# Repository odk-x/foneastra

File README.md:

# foneastra

This project is __*actively maintained*__

It defines the Foneastra controller board and software for communicating with it.

The developer [wiki](https://github.com/odk-x/tool-suite-X/wiki) (including release notes) and [issues tracker](https://github.com/odk-x/tool-suite-X/issues) are located under the [**ODK-X Tool Suite**](https://github.com/odk-x) project.

## How to contribute
If you’re new to ODK-X you can check out the documentation:
- [https://docs.odk-x.org](https://docs.odk-x.org)

Once you’re up and running, you can choose an issue to start working on from here: 
- [https://github.com/odk-x/tool-suite-X/issues](https://github.com/odk-x/tool-suite-X/issues)

Issues tagged as [good first issue](https://github.com/odk-x/tool-suite-X/issues?q=is%3Aissue+is%3Aopen+label%3A%22good+first+issue%22) should be a good place to start.

Pull requests are welcome, though please submit them against the development branch. We prefer verbose descriptions of the change you are submitting. If you are fixing a bug please provide steps to reproduce it or a link to a an issue that provides that information. If you are submitting a new feature please provide a description of the need or a link to a forum discussion about it. 

## Links for users
This document is aimed at helping developers and technical contributors. For information on how to get started as a user of ODK-X, see our [online documentation](https://docs.odk-x.org), or to learn more about the Open Data Kit project, visit [https://odk-x.org](https://odk-x.org).

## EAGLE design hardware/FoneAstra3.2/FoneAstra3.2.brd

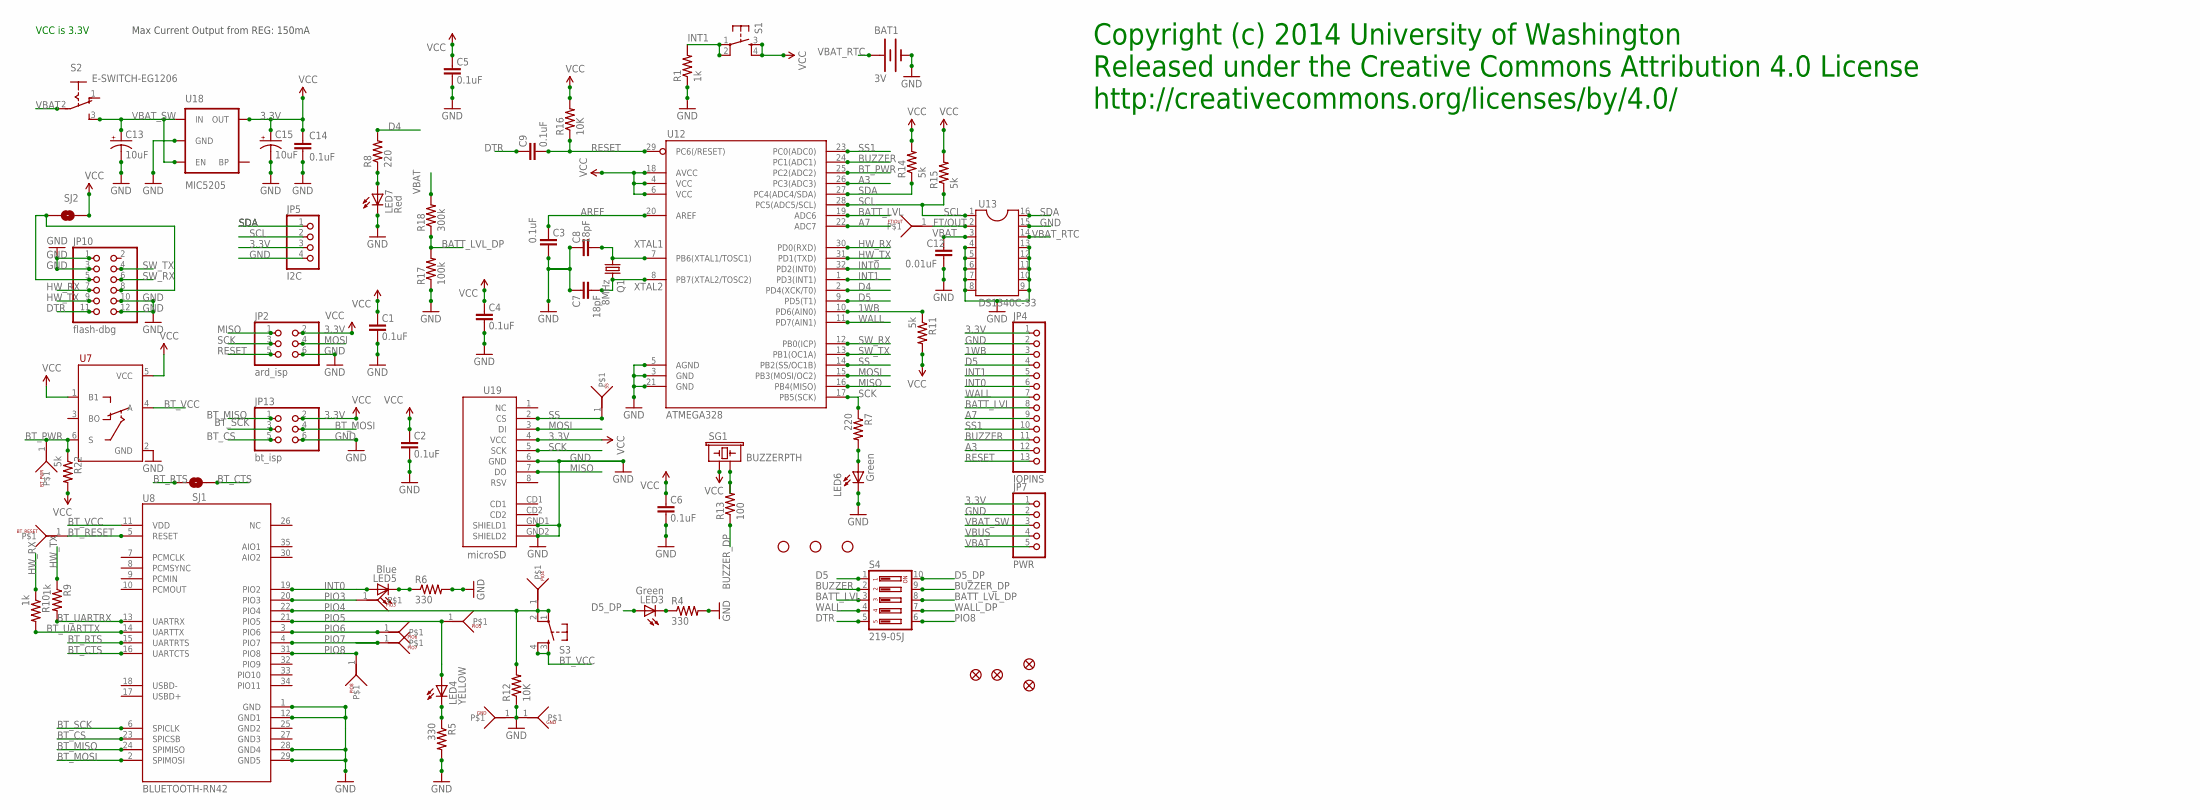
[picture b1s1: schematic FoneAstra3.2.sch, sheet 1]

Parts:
$$U3: BT_RESET; TESTPOINT
$$U4: PIO6; TESTPOINT
$$U5: PIO7; TESTPOINT
$$U6, $$U16: GND; TESTPOINT
$$U9: PIO4; TESTPOINT
$$U10: PIO3; TESTPOINT
$$U11: PIO5; TESTPOINT
$$U15: FT/OUT; TESTPOINT
BAT1: 3V; BATTCON_12MM_CURVED
BT_PWR: BT_PWR; TESTPOINT
C1, C2, C3, C4, C5, C6, C9, C14: 0.1uF; 0402-CAP
C7, C8: 18pF; 0402-CAP
C12: 0.01uF; 0402-CAP
C13, C15: 10uF; EIA3216
JP1, JP8, JP11, JP14: SPARKFUN_FIDUCIAL1.5X3; SPARKFUN_FIDUCIAL-1.5X3
JP2: ard_isp; 2X03
JP3, JP6, JP9: STAND-OFFTIGHT; STAND-OFF-TIGHT
JP4: IOPINS; 1X13M
JP5: I2C; 1X04M
JP7: PWR; 1X05M
JP10: flash-dbg; 2X06
JP13: bt_isp; 2X03
LED3, LED6: Green; LED-0603
LED4: YELLOW; LED-0603
LED5: Blue; LED-0603
LED7: Red; LED-0603
PIO8: PIO8; TESTPOINT
Q1: 8MHz; HC49/S
R1, R9, R10: 1k; 0402-RES
R4, R5, R6: 330; 0402-RES
R7, R8: 220; 0402-RES
R11, R14, R15, R22: 5k; 0402-RES
R12, R16: 10K; 0402-RES
R13: 100; 0402-RES
R17: 100k; 0402-RES
R18: 300k; 0402-RES
S1: switch; SPARKFUN_TACTILE-PTH
S2: E-SWITCH-EG1206; EG1206
S3: Reset; TACTILE_SWITCH_SMD
S4: 219-05J; CTS-219-05J
SG1: BUZZERPTH; BUZZER-12MM
SJ1, SJ2: SOLDERJUMPERNC2; SJ_2S-NOTRACE
SS: SS; TESTPOINT
U7: FSA4157AP6X; SC70-6
U8: BLUETOOTH-RN42; RN41
U12: ATMEGA328; TQFP32-08
U13: DS1340C-33; SO16L
U18: MIC5205; SOT23-5
U19: microSD; MICRO-SD-SOCKET-PP

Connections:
1WB: JP4.3, R11.1, U12.10 (PD6(AIN0)); also elsewhere on the board
3.3V: C1.2, C2.2, C4.2, C5.2, C6.2, C14.1, C15.A (+), JP2.2, JP4.1, JP5.3, JP7.1, JP13.2, R11.2, R14.2, R15.2, R16.2, R22.2, S1.3, S1.4, SG1.+ (1), SJ2.1, U7.1 (B1), U7.5 (VCC), U12.4 (VCC), U12.6 (VCC), U12.18 (AVCC), U18.5 (OUT), U19.4 (VCC); also elsewhere on the board
A3: JP4.12, U12.26 (PC3(ADC3))
A7: JP4.9, U12.22 (ADC7)
AREF: C3.2, U12.20 (AREF)
BATT_LVL: JP4.8, S4.3, U12.19 (ADC6)
BATT_LVL_DP: R17.2, R18.1, S4.8
BT_CS: JP13.5, U8.23 (SPICSB)
BT_CTS: SJ1.1, U8.16 (UARTCTS)
BT_MISO: JP13.1, U8.24 (SPIMISO)
BT_MOSI: JP13.4, U8.2 (SPIMOSI)
BT_PWR: BT_PWR.1, R22.1, U7.6 (S), U12.25 (PC2(ADC2))
BT_RESET: $$U3.1, U8.5 (RESET)
BT_RTS: SJ1.2, U8.15 (UARTRTS)
BT_SCK: JP13.3, U8.6 (SPICLK)
BT_UARTRX: R9.2, U8.13 (UARTRX)
BT_UARTTX: R10.2, U8.14 (UARTTX)
BT_VCC: S3.3, S3.4, U7.4 (A), U8.11 (VDD)
BUZZER: JP4.11, S4.2, U12.24 (PC1(ADC1))
BUZZER_DP: R13.1, S4.9
D1: LED4.C, R5.1
D4: R8.2, U12.2 (PD4(XCK/T0))
D5: JP4.4, S4.1, U12.9 (PD5(T1))
D5_DP: LED3.A, S4.10
DTR: C9.2, JP10.11, S4.5
FT/OUT: $$U15.1, U13.2
GND: $$U6.1, $$U16.1, BAT1.GND (-), C1.1, C2.1, C3.1, C4.1, C5.1, C6.1, C7.2, C8.2, C12.1, C13.C (-), C14.2, C15.C (-), JP2.6, JP4.2, JP5.4, JP7.2, JP10.1, JP10.3, JP10.10, JP10.12, JP13.6, LED6.C, LED7.C, R1.1, R4.2, R5.2, R6.2, R12.1, R17.1, U7.2 (GND), U8.1 (GND), U8.12 (GND1), U8.28 (GND4), U8.29 (GND5), U12.3 (GND), U12.5 (AGND), U12.21 (GND), U13.4, U13.5, U13.6, U13.7, U13.8, U13.9, U13.10, U13.11, U13.12, U13.13, U13.15, U18.2 (GND), U19.6 (GND), U19.GND1 (SHIELD1), U19.GND2 (SHIELD2); also elsewhere on the board
HW_RX: JP10.7, R10.1, U12.30 (PD0(RXD))
HW_TX: JP10.9, R9.1, U12.31 (PD1(TXD))
INT0: JP4.6, LED5.A, U8.19 (PIO2), U12.32 (PD2(INT0))
INT1: JP4.5, R1.2, S1.1, S1.2, U12.1 (PD3(INT1))
MISO: JP2.1, U12.16 (PB4(MISO)), U19.7 (DO)
MOSI: JP2.4, U12.15 (PB3(MOSI/OC2)), U19.3 (DI)
unnamed: R13.2, SG1.- (2)
unnamed: JP10.5, JP10.8, SJ2.2
unnamed: LED3.C, R4.1
unnamed: LED6.A, R7.2
unnamed: LED5.C, R6.1
unnamed: LED7.A, R8.1
PIO3: $$U10.1, U8.20 (PIO3)
PIO4: $$U9.1, R12.2, S3.1, S3.2, U8.22 (PIO4)
PIO5: $$U11.1, LED4.A, U8.21 (PIO5)
PIO6: $$U4.1, U8.3 (PIO6)
PIO7: $$U5.1, U8.4 (PIO7)
PIO8: PIO8.1, S4.6, U8.31 (PIO8)
RESET: C9.1, JP2.5, JP4.13, R16.1, U12.29 (PC6(/RESET))
SCK: JP2.3, R7.1, U12.17 (PB5(SCK)), U19.5 (SCK)
SCL: JP5.2, R15.1, U12.28 (PC5(ADC5/SCL)), U13.1
SDA: JP5.1, R14.1, U12.27 (PC4(ADC4/SDA)), U13.16
SS: SS.1, U12.14 (PB2(SS/OC1B)), U19.2 (CS)
SS1: JP4.10, U12.23 (PC0(ADC0))
SW_RX: JP10.6, U12.12 (PB0(ICP))
SW_TX: JP10.4, U12.13 (PB1(OC1A))
VBAT: C12.2, JP7.5, R18.2, S2.2, U13.3; also elsewhere on the board
VBAT_RTC: BAT1.PWR@1 (+), U13.14
VBAT_SW: C13.A (+), JP7.3, S2.3 (S), U18.1 (IN), U18.3 (EN)
VBUS: JP7.4; also elsewhere on the board
WALL: JP4.7, S4.4, U12.11 (PD7(AIN1))
WALL_DP: S4.7; also elsewhere on the board
XTAL1: C8.1, Q1.1, U12.7 (PB6(XTAL1/TOSC1))
XTAL2: C7.1, Q1.2, U12.8 (PB7(XTAL2/TOSC2))

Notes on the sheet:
Max Current Output from REG: 150mA
VCC is 3.3V
Copyright (c) 2014 University of Washington Released under the Creative Commons Attribution 4.0 License http://creativecommons.org/licenses/by/4.0/

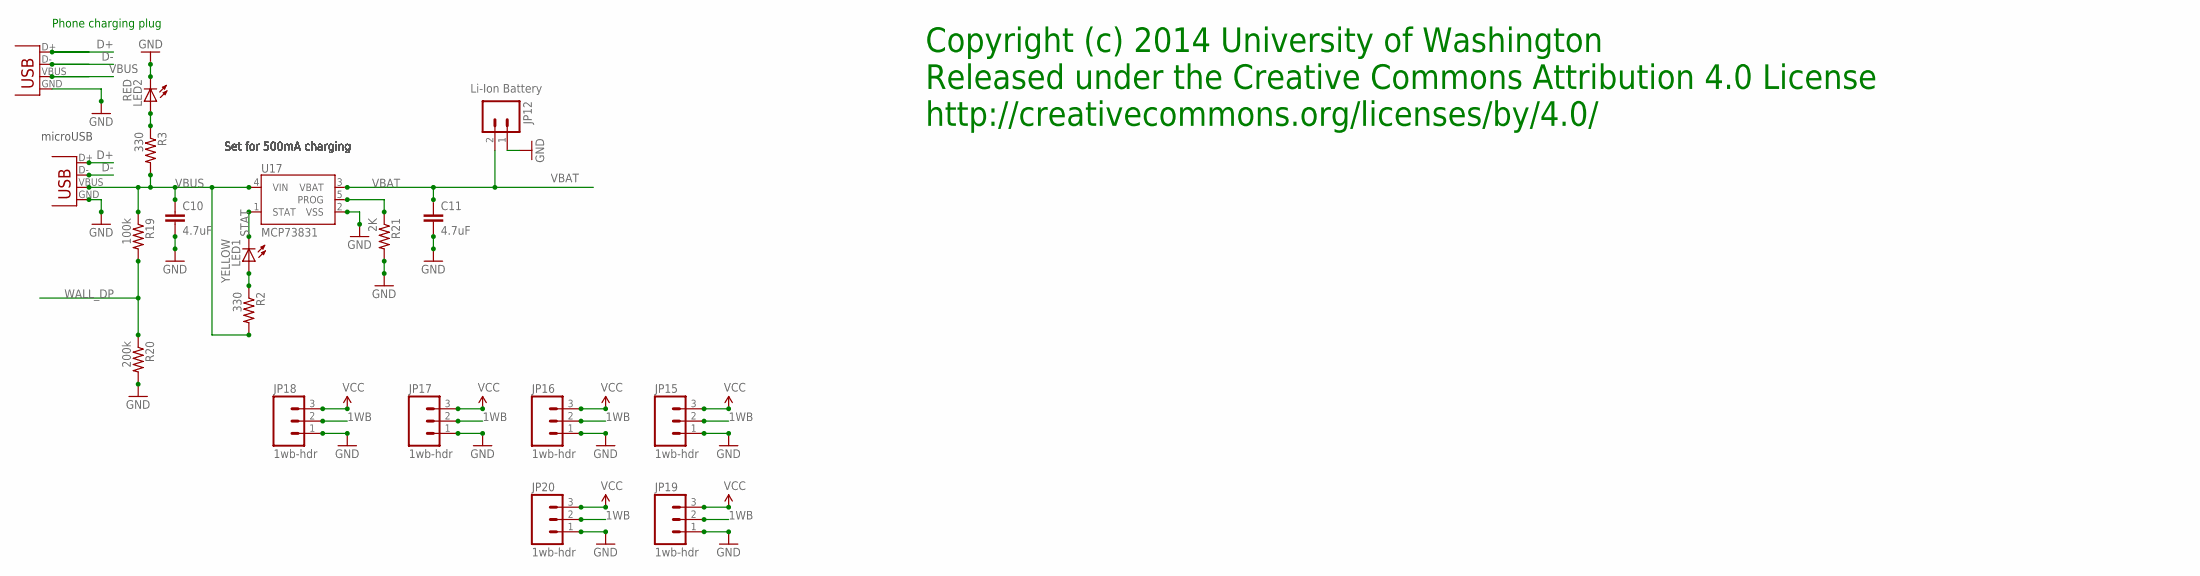
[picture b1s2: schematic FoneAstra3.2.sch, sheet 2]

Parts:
C10, C11: 4.7uF; 0402-CAP
JP12: Li-Ion Battery; SPARKFUN_JST-2-PTH
JP15, JP16, JP17, JP18, JP19, JP20: 1wb-hdr; JST-3-PTH
LED1: YELLOW; LED-0603
LED2: RED; LED-0603
R2, R3: 330; 0402-RES
R19: 100k; 0402-RES
R20: 200k; 0402-RES
R21: 2K; 0402-RES
U17: MCP73831; SOT23-5
X1, X2: Micro USB; USB-MICROB

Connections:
1WB: JP15.2, JP16.2, JP17.2, JP18.2, JP19.2, JP20.2; also elsewhere on the board
3.3V: JP15.3, JP16.3, JP17.3, JP18.3, JP19.3, JP20.3; also elsewhere on the board
D+: X1.D+, X2.D+
D-: X1.D-, X2.D-
GND: C10.2, C11.2, JP12.1, JP15.1, JP16.1, JP17.1, JP18.1, JP19.1, JP20.1, LED2.C, R20.2, R21.2, U17.2 (VSS), X1.GND, X2.GND; also elsewhere on the board
unnamed: LED2.A, R3.1
unnamed: LED1.A, R2.1
PROG: R21.1, U17.5 (PROG)
STAT: LED1.C, U17.1 (STAT)
VBAT: C11.1, JP12.2, U17.3 (VBAT); also elsewhere on the board
VBUS: C10.1, R2.2, R3.2, R19.1, U17.4 (VIN), X1.VBUS, X2.VBUS; also elsewhere on the board
WALL_DP: R19.2, R20.1; also elsewhere on the board

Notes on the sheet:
Set for 500mA charging
microUSB
Phone charging plug
Copyright (c) 2014 University of Washington Released under the Creative Commons Attribution 4.0 License http://creativecommons.org/licenses/by/4.0/

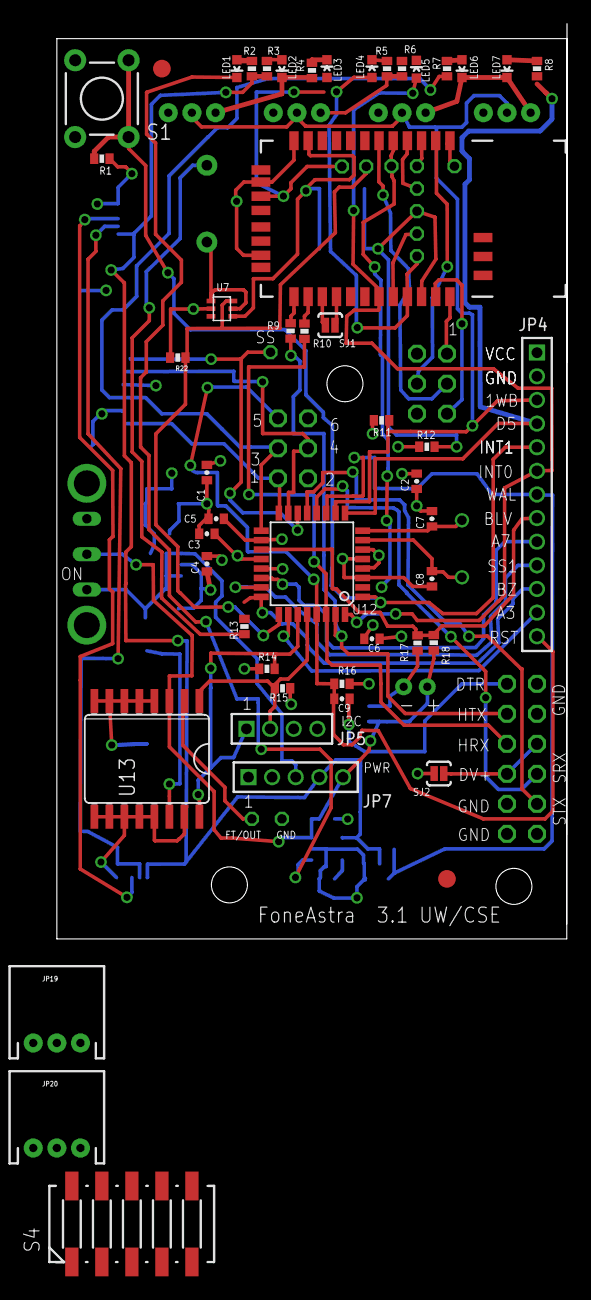
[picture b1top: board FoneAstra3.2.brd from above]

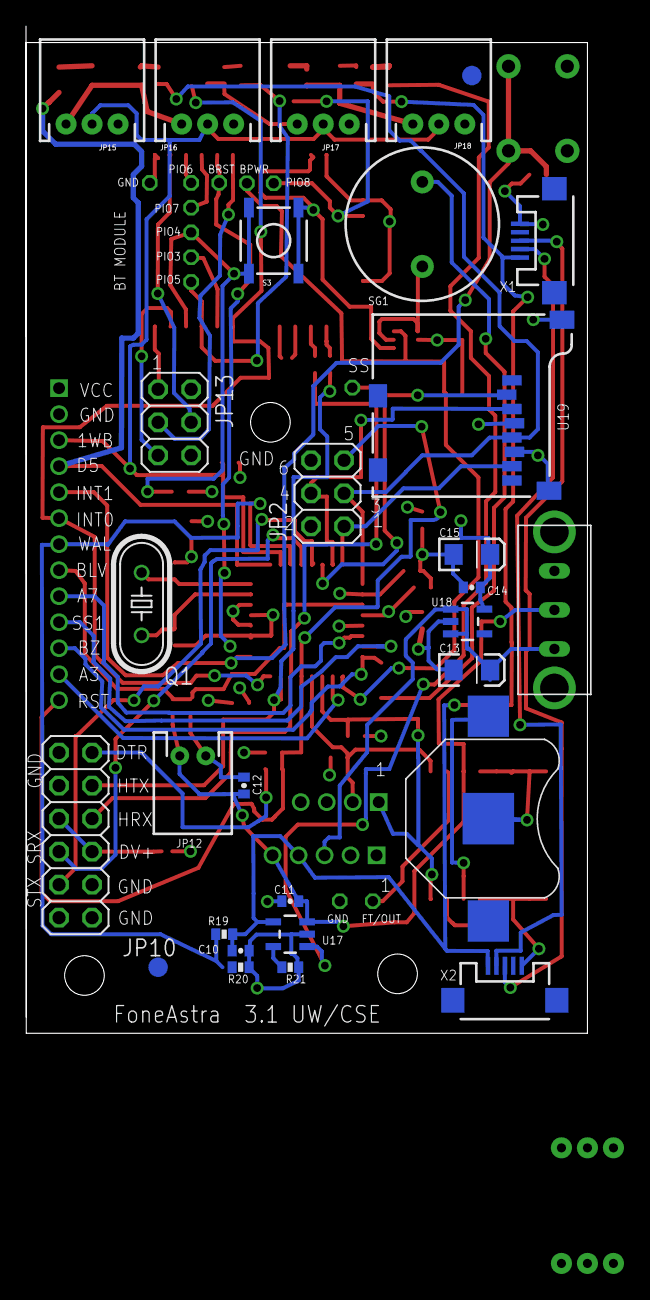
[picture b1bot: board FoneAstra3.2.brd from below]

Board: 4 copper layers, 43.2 x 77.5 mm, 94 parts (29 on the bottom side), 67 nets.

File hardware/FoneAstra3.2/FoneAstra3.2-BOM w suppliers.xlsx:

Part | Value | Device | Package | Description | Digikey/SFE Part | Additional notes
$$U3 | BT_RESET | TESTPOINT | TESTPOINT
$$U4 | PIO6 | TESTPOINT | TESTPOINT
$$U5 | PIO7 | TESTPOINT | TESTPOINT
$$U6 | GND | TESTPOINT | TESTPOINT
$$U9 | PIO4 | TESTPOINT | TESTPOINT
$$U10 | PIO3 | TESTPOINT | TESTPOINT
$$U11 | PIO5 | TESTPOINT | TESTPOINT
$$U15 | FT/OUT | TESTPOINT | TESTPOINT
$$U16 | GND | TESTPOINT | TESTPOINT
BAT1 | 3V | BATTERY | BATTCON_12MM_CURVED | Battery Holders | SFE: http://www.sparkfun.com/products/10592
BT_PWR | BT_PWR | TESTPOINT | TESTPOINT
C1 | 0.1uF | CAP0402-CAP | 0402-CAP | Capacitor | 445-3445-1-ND
C2 | 0.1uF | CAP0402-CAP | 0402-CAP | Capacitor | 445-3445-1-ND
C3 | 0.1uF | CAP0402-CAP | 0402-CAP | Capacitor | 445-3445-1-ND
C4 | 0.1uF | CAP0402-CAP | 0402-CAP | Capacitor | 445-3445-1-ND
C5 | 0.1uF | CAP0402-CAP | 0402-CAP | Capacitor | 445-3445-1-ND
C6 | 0.1uF | CAP0402-CAP | 0402-CAP | Capacitor | 445-3445-1-ND
C7 | 18pF | CAP0402-CAP | 0402-CAP | Capacitor | 445-1238-1-ND
C8 | 18pF | CAP0402-CAP | 0402-CAP | Capacitor | 445-1238-1-ND
C9 | 0.1uF | CAP0402-CAP | 0402-CAP | Capacitor | 445-3445-1-ND
C10 | 4.7uF | CAP0402-CAP | 0402-CAP | Capacitor | 445-7395-1-ND
C11 | 4.7uF | CAP0402-CAP | 0402-CAP | Capacitor | 445-7395-1-ND
C12 | 0.01uF | CAP0402-CAP | 0402-CAP | Capacitor | 399-4875-1-ND
C13 | 10uF | CAP_POL1206 | EIA3216 | Capacitor Polarized | 399-3687-1-ND
C14 | 0.1uF | CAP0402-CAP | 0402-CAP | Capacitor | 445-3445-1-ND
C15 | 10uF | CAP_POL1206 | EIA3216 | Capacitor Polarized | 399-3687-1-ND
JP1 | SPARKFUN_FIDUCIAL1.5X3 | SPARKFUN_FIDUCIAL1.5X3 | SPARKFUN_FIDUCIAL-1.5X3 | Fiducial Alignment Points
JP2 | ard_isp | PINHD-2X3 | 2X03 | PIN HEADER | 609-3218-ND
JP3 | STAND-OFFTIGHT | STAND-OFFTIGHT | STAND-OFF-TIGHT | #4 Stand Off
JP4 | IOPINS | PINHD-1X13M | 1X13M | PIN HEADER | 3M9402-ND + 3M9401-ND
JP5 | I2C | PINHD-1X4M | 1X04M | PIN HEADER | 3M9399-ND
JP6 | STAND-OFFTIGHT | STAND-OFFTIGHT | STAND-OFF-TIGHT | #4 Stand Off
JP7 | PWR | PINHD-1X5M | 1X05M | PIN HEADER | 3M9400-ND
JP8 | SPARKFUN_FIDUCIAL1.5X3 | SPARKFUN_FIDUCIAL1.5X3 | SPARKFUN_FIDUCIAL-1.5X3 | Fiducial Alignment Points
JP9 | STAND-OFFTIGHT | STAND-OFFTIGHT | STAND-OFF-TIGHT | #4 Stand Off
JP10 | flash-dbg | PINHD-2X6 | 2X06 | PIN HEADER | 609-3219-ND
JP11 | SPARKFUN_FIDUCIAL1.5X3 | SPARKFUN_FIDUCIAL1.5X3 | SPARKFUN_FIDUCIAL-1.5X3 | Fiducial Alignment Points
JP12 | Li-Ion Battery | SPARKFUN_M02JST-PTH-2 | SPARKFUN_JST-2-PTH | Header 2 | A100043-ND
JP13 | bt_isp | PINHD-2X3 | 2X03 | PIN HEADER | DO NOT assemble this
JP14 | SPARKFUN_FIDUCIAL1.5X3 | SPARKFUN_FIDUCIAL1.5X3 | SPARKFUN_FIDUCIAL-1.5X3 | Fiducial Alignment Points
JP15 | 1wb-hdr | M03JST-PTH | JST-3-PTH | Header 3 | 455-1720-ND
JP16 | 1wb-hdr | M03JST-PTH | JST-3-PTH | Header 3 | 455-1720-ND
JP17 | 1wb-hdr | M03JST-PTH | JST-3-PTH | Header 3 | 455-1720-ND
JP18 | 1wb-hdr | M03JST-PTH | JST-3-PTH | Header 3 | 455-1720-ND
LED1 | YELLOW | LED0603 | LED-0603 | LEDs | 751-1186-1-ND
LED2 | RED | LED0603 | LED-0603 | LEDs | 404-1000-1-ND
LED3 | Green | LED0603 | LED-0603 | LEDs | 404-1004-1-ND
LED4 | YELLOW | LED0603 | LED-0603 | LEDs | 751-1186-1-ND
LED5 | Blue | LED0603 | LED-0603 | LEDs | 160-1827-1-ND
LED6 | Green | LED0603 | LED-0603 | LEDs | 404-1004-1-ND
LED7 | Red | LED0603 | LED-0603 | LEDs | 404-1000-1-ND
PIO8 | PIO8 | TESTPOINT | TESTPOINT
Q1 | 8MHz | CRYSTALHC49S | HC49/S | CRYSTAL | CTX900-ND
R1 | 1k | RESISTOR0402-RES | 0402-RES | Resistor | P1.0KJCT-ND
R2 | 330 | RESISTOR0402-RES | 0402-RES | Resistor | P330JCT-ND
R3 | 330 | RESISTOR0402-RES | 0402-RES | Resistor | P330JCT-ND
R4 | 330 | RESISTOR0402-RES | 0402-RES | Resistor | P330JCT-ND
R5 | 330 | RESISTOR0402-RES | 0402-RES | Resistor | P330JCT-ND
R6 | 330 | RESISTOR0402-RES | 0402-RES | Resistor | P330JCT-ND
R7 | 220 | RESISTOR0402-RES | 0402-RES | Resistor | P220LCT-ND
R8 | 220 | RESISTOR0402-RES | 0402-RES | Resistor | P220LCT-ND
R9 | 1k | RESISTOR0402-RES | 0402-RES | Resistor | P1.0KJCT-ND
R10 | 1k | RESISTOR0402-RES | 0402-RES | Resistor | P1.0KJCT-ND
R11 | 5k | RESISTOR0402-RES | 0402-RES | Resistor | P5.1KJCT-ND
R12 | 10K | RESISTOR0402-RES | 0402-RES | Resistor | P10KJCT-ND
R13 | 100 | RESISTOR0402-RES | 0402-RES | Resistor | P100JCT-ND
R14 | 5k | RESISTOR0402-RES | 0402-RES | Resistor | P5.1KJCT-ND
R15 | 5k | RESISTOR0402-RES | 0402-RES | Resistor | P5.1KJCT-ND
R16 | 10K | RESISTOR0402-RES | 0402-RES | Resistor | P10KJCT-ND
R17 | 100k | RESISTOR0402-RES | 0402-RES | Resistor | P100KJCT-ND
R18 | 300k | RESISTOR0402-RES | 0402-RES | Resistor | P300KJCT-ND
R19 | 100k | RESISTOR0402-RES | 0402-RES | Resistor | P100KJCT-ND
R20 | 200k | RESISTOR0402-RES | 0402-RES | Resistor | P200KJCT-ND
R21 | 2K | RESISTOR0402-RES | 0402-RES | Resistor | P2.0KJCT-ND
R22 | 5k | RESISTOR0402-RES | 0402-RES | Resistor | P5.1KJCT-ND
S1 | switch | SPARKFUN_TAC_SWITCHPTH | SPARKFUN_TACTILE-PTH | Momentary Switch | EG1831-ND
S2 | E-SWITCH-EG1206 | E-SWITCH-EG1206 | EG1206 | Rt Angle slide switch | EG1916-ND
S3 | Reset | TAC_SWITCHSMD | TACTILE_SWITCH_SMD | Momentary Switch | SFE: https://www.sparkfun.com/products/8720
SG1 | BUZZERPTH | BUZZERPTH | BUZZER-12MM | Buzzer 12mm | 445-2525-1-ND
SJ1 |  | SOLDERJUMPERNC2 | SJ_2S-NOTRACE | Solder Jumper
SJ2 |  | SOLDERJUMPERNC2 | SJ_2S-NOTRACE | Solder Jumper
SS | SS | TESTPOINT | TESTPOINT
U7 | FSA4157AP6X | FSA4157AP6X | SC70-6 | IC Switch SPDT | FSA4157AP6XCT-ND
U8 | BLUETOOTH-RN42 | BLUETOOTH-RN41" | RN41 | RN42 Bluetooth SMD | SFE: https://www.sparkfun.com/products/10253
U12 | ATMEGA328 | ATMEGA168 | TQFP32-08 | ATMega328P Processor | ATMEGA328P-AU-ND
U13 | DS1340C-33 | DS1340C-33 | SO16L | I2C RTC | DS1340C-33#-ND
U17 | MCP73831 | MCP73831 | SOT23-5 | Microchip's MCP73831 | MCP73831T-2ACI/OTCT-ND
U18 | MIC5205 | V_REG_LDOSMD | SOT23-5 | Voltage Regulator LDO | 576-1259-1-ND
U19 | microSD | USD-SOCKETSMD | MICRO-SD-SOCKET-PP | microSD Socket | SFE: https://www.sparkfun.com/products/127
X1 | Micro USB | USB-MICROB | USB-MICROB | USB Connectors | 609-4053-1-ND
X2 | Micro USB | USB-MICROB | USB-MICROB | USB Connectors | 609-4053-1-ND
 | Other parts
 | micro USB AB charging cable | Cable | AE10424-ND | cable to charge phone via board | AE10424-ND
 | Li-ion battery | 2 pin JST terminated Li-ion battery |  |  | Example SFE part:https://www.sparkfun.com/products/8483 | Need to find a similar, cheaper battery
 | RTC backup battery | 12 mm coin cell |  |  | Example SFE part: https://www.sparkfun.com/products/337 | Same comment as above
 | Temperature probe | DS18b20 temp probe |  |  | Example SFE part: https://www.sparkfun.com/products/11050 | Chinese vendors on ebay sell similar probes of varying lengths for much cheaper
 | temp probe-board connector | 3-pin JST cable |  |  | Example SFE part: https://www.sparkfun.com/products/9915
 | Temperature sensor | DS18b20 temp sensor |  |  | Example SFE part: https://www.sparkfun.com/products/245 | In some use cases the bare temp sensor is soldered directly on to the board
 | microSD card | 4GB will be sufficient |  |  | Example amazon part: http://www.amazon.com/Kingston-microSDHC-Memory-SDC4-8GBET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
 | Enclosure

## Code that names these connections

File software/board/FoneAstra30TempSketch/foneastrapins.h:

/*
 * Copyright (C) 2014 University of Washington
 *
 * Licensed under the Apache License, Version 2.0 (the "License"); you may not
 * use this file except in compliance with the License. You may obtain a copy of
 * the License at
 *
 * http://www.apache.org/licenses/LICENSE-2.0
 *
 * Unless required by applicable law or agreed to in writing, software
 * distributed under the License is distributed on an "AS IS" BASIS, WITHOUT
 * WARRANTIES OR CONDITIONS OF ANY KIND, either express or implied. See the
 * License for the specific language governing permissions and limitations under
 * the License.
 */

#ifndef __FONEASTRA_PINS_H__
#define __FONEASTRA_PINS_H__

/*
this file maps pins on the FoneAstra board to an AtMega328 based Arduino (Uno, mini, pro mini)
Arduino-ATMega pin mapping available at:
http://www.arduino.cc/en/Hacking/PinMapping168
 */

//SS1_PIN

//BUZZER_PIN: an audio buzzer is connected to this pin. 

//BT_PWR_PIN: this controls power to the BT module. driving this high turns the module on, low is off.

//A3_PIN

//I2C SDA, SCL pins already defined in Contents/Resources/Java/hardware/arduino/variants/standard/pins_arduino.h 

//BATT_LVL_PIN: this is a voltage divider and used for an approximate measure of battery charge

//A7_PIN

//INT0_PIN: goes high when a BT device connects (blue LED goes on), low otherwise. 

//INT1_PIN: connected to a tactile switch. Goes high when the switch is pressed.

//BT_RESET_PIN: this pin can reset the BT module.  

//D5_PIN

//ONEWIRE_PIN: 1-wire sensors are connected to this pin. The temperature sensor used in HMB & VAX apps is a 1wb sensor.  

//WALL_PIN: high when a usb charger is connected to the board, low otherwise. 
//
//the BT module is connected to ATMega's h/w UART, so for apps that use the BT module, we have a software UART 
//for the serial console. foneastra's UARTs are accessible on a 2x6 male header. The pins on the inner row are the
//HW UART & used for downloading code on the board. The pins on the outer row are the SW UART & can be used with 
//the serial console if HW UART is being used for BT communications
//
//SW_UART_RX: the rx pin of the s/w uart 

//SW_UART_TX: the tx pin of the h/w uart. 

//SPI SS, MOSI, MISO, SCK pns already defined in pins_arduino.h

#define SS1_PIN A0
#define BUZZER_PIN A1
#define BT_PWR_PIN A2
#define A3_PIN A3

//I2C pins. Already defined in Contents/Resources/Java/hardware/arduino/variants/standard/pins_arduino.h
//#define SDA A4
//#define SCL A5

#define BATT_LVL_PIN A6
#define A7_PIN A7

#define HW_UART_RX_PIN 0
#define HW_UART_TX_PIN 1
#define INT0_PIN 2
#define INT1_PIN 3
#define BT_RESET_PIN 4
#define D5_PIN 5
#define ONEWIRE_PIN 6
#define WALL_PIN 7
#define SW_UART_RX_PIN 8
#define SW_UART_TX_PIN 9

#define RED_LED_PIN D5_PIN
#define GREEN_LED_PIN SCK

//SPI pins. Already defined in Contents/Resources/Java/hardware/arduino/variants/standard/pins_arduino.h
//#define SS 10
//#define MOSI 11
//#define MISO 12
//#define SCK 13

#endif

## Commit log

2014-08-12 Initial checkin
2014-08-12 Initial checkin for android code
2014-08-13 Sensor demo with androidcommon version rev 121 US Army Preparedness Demo 2014
2014-08-13 The EAGLE projects for FoneAstra 3.1 and 3.2
2014-08-14 STL files for the enclosure
2014-08-15 added pdfs for schematics, updated v3.2 changes.txt
2014-08-16 cleaning out bad binary checked in
2014-08-16 hope
2014-08-16 Possible speed improvement
2014-08-16 remove jar that is version specific
2014-10-06 Commit ignore message
2014-11-05 Change to make the temperature sensor demo work
2014-11-07 Added tag TechCon Demo 11-2014 for changeset 2caf6a877fd2
2015-08-11 Removed reference to .iml files in README.
2015-08-11 Migrated from .hgignore to .gitignore
2016-08-10 port projects to Gradle
2017-03-29 Fix sensorConnect and put in temp fix for startSensor
2021-03-30 Added contributor paragraph and updated links

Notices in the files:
parts and their libraries:
SparkFun-Connectors: Licensing: CC v3.0 Share-Alike You are welcome to use this library for commercial purposes.
